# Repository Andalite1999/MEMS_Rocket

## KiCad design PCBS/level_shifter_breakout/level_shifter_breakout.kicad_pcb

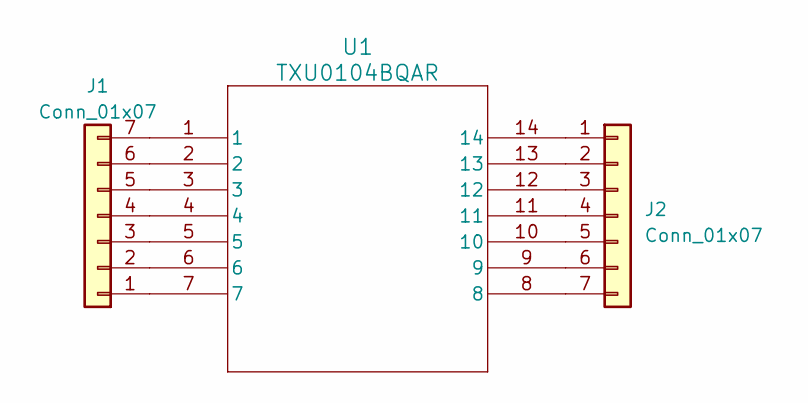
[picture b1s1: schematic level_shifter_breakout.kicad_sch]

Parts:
J1, J2: Conn_01x07; PinHeader_1x07_P2.54mm_Vertical
U1: TXU0104BQAR; HTSSOP-14-1EP_4.4x5mm_P0.65mm_EP3.4x5mm_Mask3x3.1mm

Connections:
unnamed: J1.1, U1.7
unnamed: J1.2, U1.6
unnamed: J1.3, U1.5
unnamed: J1.4, U1.4
unnamed: J1.5, U1.3
unnamed: J1.6, U1.2
unnamed: J1.7, U1.1
unnamed: J2.1, U1.14
unnamed: J2.2, U1.13
unnamed: J2.3, U1.12
unnamed: J2.4, U1.11
unnamed: J2.5, U1.10
unnamed: J2.6, U1.9
unnamed: J2.7, U1.8

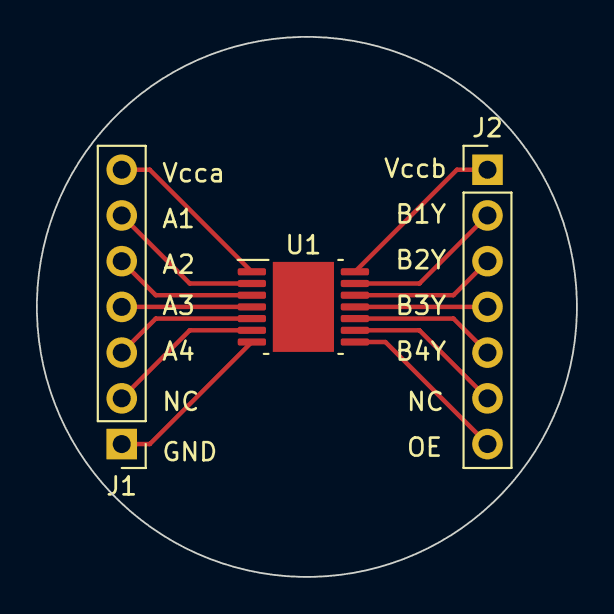
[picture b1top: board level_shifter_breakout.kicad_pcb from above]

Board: 2 copper layers, 30.0 x 30.0 mm, 3 parts (0 on the bottom side), 14 nets.

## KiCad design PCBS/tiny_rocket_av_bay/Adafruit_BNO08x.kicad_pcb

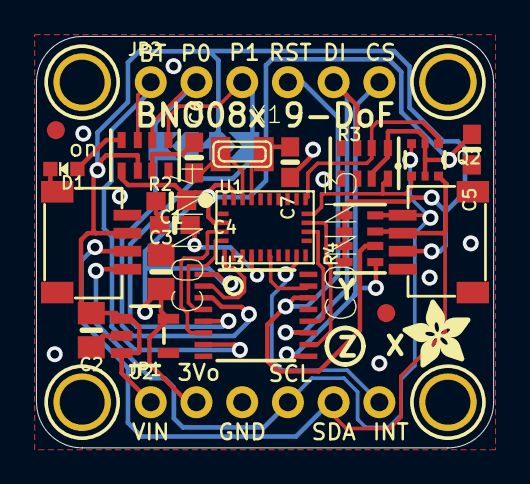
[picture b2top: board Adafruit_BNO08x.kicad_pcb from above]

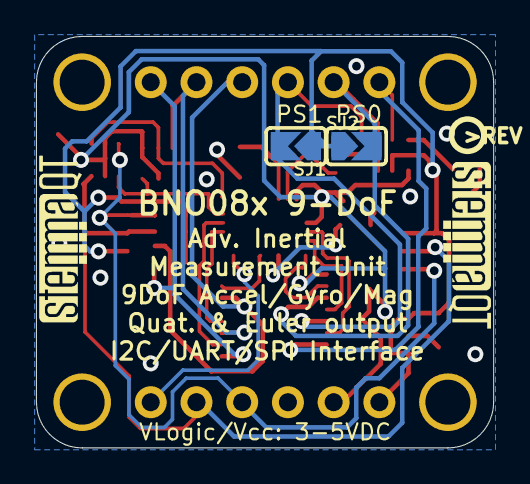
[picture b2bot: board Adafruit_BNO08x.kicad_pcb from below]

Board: 2 copper layers, 25.4 x 22.9 mm, 32 parts (5 on the bottom side), 24 nets.

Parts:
C1, C4, C5: 0.1uF; 0603-NO
C2, C3: 10uF; 0805-NO
C6, C7: 22pF; 0603-NO
CONN3, CONN4: STEMMA_I2C_QT; JST_SH4
D1: GREEN; CHIPLED_0603_NOOUTLINE
FID3, FID4: FIDUCIAL_1MM
JP1, JP2: 1X06_ROUND_70
Q2: BSS138; SOT363
R2, R3, R4: 10K; RESPACK_4X0603
SJ1: PS1; SOLDERJUMPER_ARROW_NOPASTE
SJ2: PS0; SOLDERJUMPER_ARROW_NOPASTE
U1: BNO080
U2: AP2112K-3.3; SOT23-5
U3: 74AHC4050; TSSOP16
U$1, U$17, U$19, U$21: MOUNTINGHOLE2.5; MOUNTINGHOLE_2.5_PLATED
U$22: ADAFRUIT_3.5MM
U$25: PCBFEAT-REV-040
U$30, U$31: STEMMAQT
X1: 32.768; XTAL3215

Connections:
3.3V: C1.1, C3.1, C5.1, JP1.2, Q2.2, Q2.5, R2.5, R3.3, R3.5, U1.3, U1.28, U2.5, U3.1
BOOT: JP2.1, R2.3, U3.7
BOOT_3V: U1.4, U3.6
CAP: C4.2, U1.9
CS: JP2.6, R4.1, U3.9
CS_3V: U1.18, U3.10
GND: C1.2, C2.2, C3.2, C4.1, C5.2, C6.2, C7.2, CONN3.1, CONN3.MT1, CONN3.MT2, CONN4.1, CONN4.MT1, CONN4.MT2, D1.C, JP1.3, R2.7, R2.8, R3.1, R3.2, R3.8, U1.2, U1.10, U1.25, U2.2, U3.8
INT: JP1.6, U1.14
MOSI: JP2.5, R3.7, U3.11
MOSI_3V: U1.17, U3.12
unnamed: D1.A, R2.4
PS0: JP2.2, R2.2, SJ2.2, U3.3
PS0_3V: U1.6, U3.2
PS1: JP2.3, R2.1, SJ1.2, U3.5
PS1_3V: U1.5, U3.4
RST: JP2.4, R4.2, U3.14
RST_3V: U1.11, U3.15
SCL/SCK/RX: CONN3.4, CONN4.4, JP1.4, Q2.6, R4.4
SCL_3V: Q2.1, R3.4, U1.19
SDA/MISO/TX: CONN3.3, CONN4.3, JP1.5, Q2.3, R4.3
SDA_3V: Q2.4, R3.6, U1.20
VCC: C2.1, CONN3.2, CONN4.2, JP1.1, R2.6, R4.5, R4.6, R4.7, R4.8, SJ1.1, SJ2.1, U2.1, U2.3
XIN: C6.1, U1.27, X1.P$1
XOUT: C7.1, U1.26, X1.P$2

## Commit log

2023-11-05 added kicad files
2023-11-05 reorganization
2023-11-13 balloon tracker with transition between high res and high speed modes
2023-11-13 IMU tracking and cleanup
2023-11-13 working version of tracker
2023-11-19 preliminary control
2023-11-20 added velocity tracking, orientation tracking
2024-01-30 added openrocket files
2024-02-26 big changes to IMU logic
2024-03-03 more data
2024-03-11 simulation milestone
2024-03-18 added quaternions
2024-04-01 new rocket model
2024-04-28 broken up firmware
2024-04-28 added arduino protype files
2024-04-28 temp fix
